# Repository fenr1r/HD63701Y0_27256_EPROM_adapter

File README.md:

# HD63701Y0_27256_EPROM_adapter

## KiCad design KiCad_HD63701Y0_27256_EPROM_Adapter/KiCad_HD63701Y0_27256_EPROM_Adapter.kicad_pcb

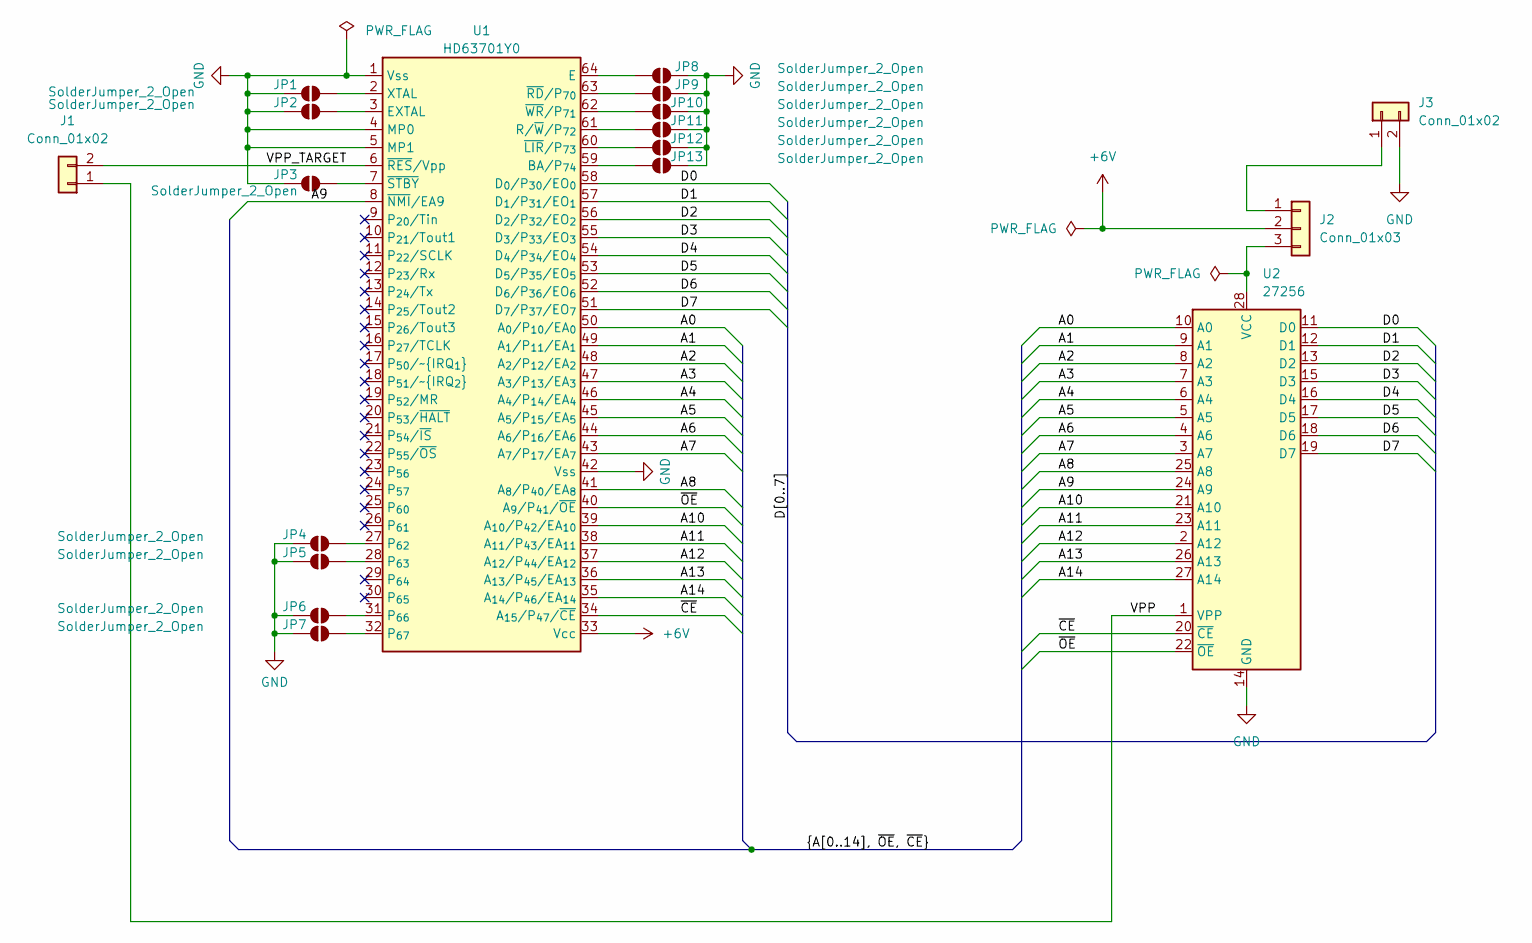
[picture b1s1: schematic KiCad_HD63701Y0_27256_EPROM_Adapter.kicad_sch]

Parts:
J1, J3: Conn_01x02; PinHeader_1x02_P2.54mm_Vertical
J2: Conn_01x03; PinHeader_1x03_P2.54mm_Vertical
JP1, JP2, JP3, JP4, JP5, JP6, JP7, JP8, JP9, JP10, JP11, JP12, JP13: SolderJumper_2_Open; SolderJumper-2_P1.3mm_Open_RoundedPad1.0x1.5mm
U1: HD63701Y0; DIP_Socket-64_Shrink_1.78mm_W20.70mm_3M_264-1300-00_0602J
U2: 27256; DIP-28_W15.24mm_Socket_LongPads

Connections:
+6V: J2.2, U1.33 (Vcc)
/A0: U1.50 (A_{0}/P_{10}/EA_{0}), U2.10 (A0)
/A1: U1.49 (A_{1}/P_{11}/EA_{1}), U2.9 (A1)
/A2: U1.48 (A_{2}/P_{12}/EA_{2}), U2.8 (A2)
/A3: U1.47 (A_{3}/P_{13}/EA_{3}), U2.7 (A3)
/A4: U1.46 (A_{4}/P_{14}/EA_{4}), U2.6 (A4)
/A5: U1.45 (A_{5}/P_{15}/EA_{5}), U2.5 (A5)
/A6: U1.44 (A_{6}/P_{16}/EA_{6}), U2.4 (A6)
/A7: U1.43 (A_{7}/P_{17}/EA_{7}), U2.3 (A7)
/A8: U1.41 (A_{8}/P_{40}/EA_{8}), U2.25 (A8)
/A9: U1.8 (~NMI/EA9), U2.24 (A9)
/A10: U1.39 (A_{10}/P_{42}/EA_{10}), U2.21 (A10)
/A11: U1.38 (A_{11}/P_{43}/EA_{11}), U2.23 (A11)
/A12: U1.37 (A_{12}/P_{44}/EA_{12}), U2.2 (A12)
/A13: U1.36 (A_{13}/P_{45}/EA_{13}), U2.26 (A13)
/A14: U1.35 (A_{14}/P_{46}/EA_{14}), U2.27 (A14)
/D0: U1.58 (D_{0}/P_{30}/EO_{0}), U2.11 (D0)
/D1: U1.57 (D_{1}/P_{31}/EO_{1}), U2.12 (D1)
/D2: U1.56 (D_{2}/P_{32}/EO_{2}), U2.13 (D2)
/D3: U1.55 (D_{3}/P_{33}/EO_{3}), U2.15 (D3)
/D4: U1.54 (D_{4}/P_{34}/EO_{4}), U2.16 (D4)
/D5: U1.53 (D_{5}/P_{35}/EO_{5}), U2.17 (D5)
/D6: U1.52 (D_{6}/P_{36}/EO_{6}), U2.18 (D6)
/D7: U1.51 (D_{7}/P_{37}/EO_{7}), U2.19 (D7)
/VPP: J1.1, U2.1 (VPP)
/VPP_TARGET: J1.2, U1.6 (~RES/Vpp)
/~CE: U1.34 (A_{15}/P_{47}/~CE), U2.20 (~CE)
/~OE: U1.40 (A_{9}/P_{41}/~OE), U2.22 (~OE)
GND: J3.2, JP1.1 (A), JP2.1 (A), JP3.1 (A), JP4.1 (A), JP5.1 (A), JP6.1 (A), JP7.1 (A), JP8.1 (A), JP9.1 (A), JP10.1 (A), JP11.1 (A), JP12.1 (A), JP13.1 (A), U1.1 (Vss), U1.4 (MP0), U1.5 (MP1), U1.42 (Vss), U2.14 (GND)
unnamed: J2.1, J3.1
unnamed: J2.3, U2.28 (VCC)
unnamed: JP1.2 (B), U1.2 (XTAL)
unnamed: JP2.2 (B), U1.3 (EXTAL)
unnamed: JP3.2 (B), U1.7 (~STBY)
unnamed: JP4.2 (B), U1.27 (P_{62})
unnamed: JP5.2 (B), U1.28 (P_{63})
unnamed: JP6.2 (B), U1.31 (P_{66})
unnamed: JP7.2 (B), U1.32 (P_{67})
unnamed: JP8.2 (B), U1.64 (E)
unnamed: JP9.2 (B), U1.63 (~RD/P_{70})
unnamed: JP10.2 (B), U1.62 (~WR/P_{71})
unnamed: JP11.2 (B), U1.61 (R/~W/P_{72})
unnamed: JP12.2 (B), U1.60 (~LIR/P_{73})
unnamed: JP13.2 (B), U1.59 (BA/P_{74})

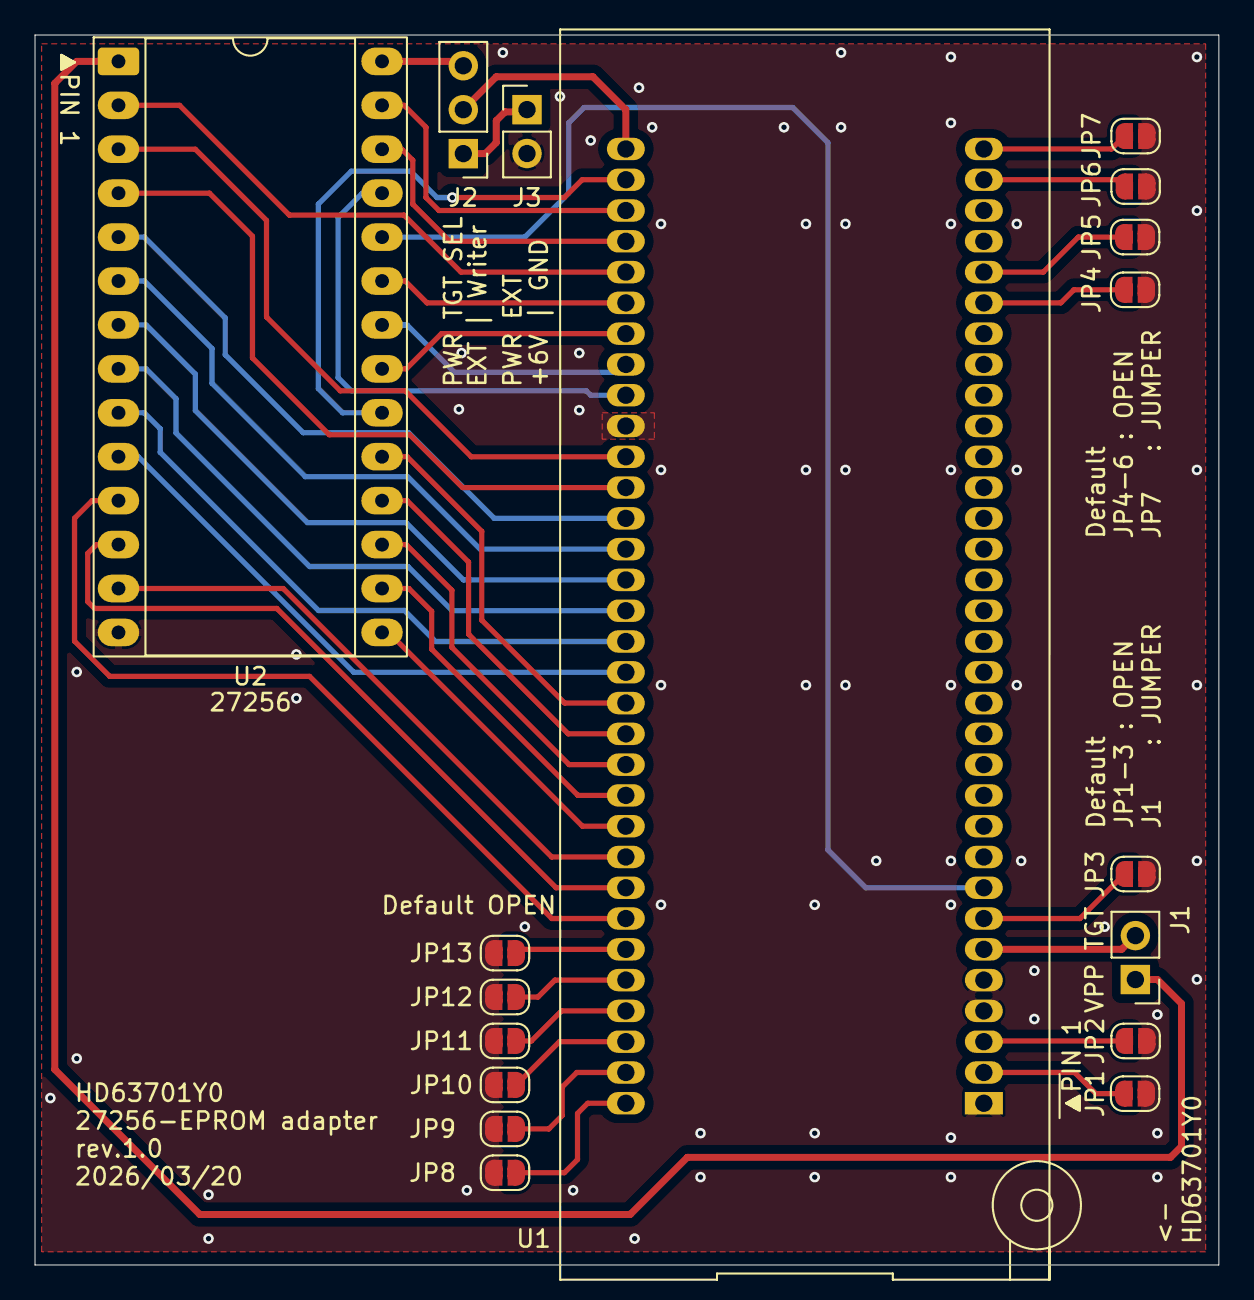
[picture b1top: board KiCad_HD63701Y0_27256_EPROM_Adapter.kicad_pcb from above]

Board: 2 copper layers, 68.5 x 71.1 mm, 18 parts (0 on the bottom side), 44 nets.

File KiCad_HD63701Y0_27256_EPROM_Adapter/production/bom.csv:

Designator,Footprint,Quantity,Value,LCSC Part #
"J1, J3",PinHeader_1x02_P2.54mm_Vertical,2,Conn_01x02,
J2,PinHeader_1x03_P2.54mm_Vertical,1,Conn_01x03,
U1,DIP_Socket-64_Shrink_1.78mm_W20.70mm_3M_264-1300-00_0602J,1,HD63701Y0,
U2,DIP-28_W15.24mm_Socket_LongPads,1,27256,
